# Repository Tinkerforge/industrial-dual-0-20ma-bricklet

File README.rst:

Industrial Dual 0-20mA Bricklet
===============================

This repository contains the firmware source code and the hardware design
files. The documentation generator configs can be found at
https://github.com/Tinkerforge/generators

Repository Content
------------------

software/:
 * examples/: Examples for all supported languages
 * build/: Compiled files
 * src/: Source code of firmware
 * Makefile: Makefile to build project

hardware/:
 * Contains KiCad project files and additionally schematics as PDF

datasheets/:
 * Contains datasheets for sensors and complex ICs that are used

Hardware
--------

The hardware is designed with the open source EDA Suite KiCad
(http://www.kicad.org). Before you are able to open the files,
you have to install the Tinkerforge kicad-libraries
(https://github.com/Tinkerforge/kicad-libraries). You can either clone
them directly in hardware/ or clone them in a separate folder and
symlink them into hardware/
(ln -s kicad_path/kicad-libraries project_path/hardware). After that you
can open the .pro file in hardware/ with KiCad and from there view and
modify the schematics and the PCB layout.

Software
--------

If you want to do your own Brick/Bricklet firmware development we highly
recommend that you use our build environment setup script and read the
tutorial (https://www.tinkerforge.com/en/doc/Tutorials/Tutorial_Build_Environment/Tutorial.html).

To compile the C code we recommend you to install the newest GNU Arm Embedded
Toolchain (https://launchpad.net/gcc-arm-embedded/+download).
You also need to install bricklib (https://github.com/Tinkerforge/bricklib)
and brickletlib (https://github.com/Tinkerforge/brickletlib).

You can either clone it directly in software/src/ or clone it in a
separate folder and symlink it into software/src/
(ln -s bricklib_path/bricklib project_path/software/src/ and
ln -s brickletlib_path/brickletlib project_path/software/src/).
Finally make sure to have CMake installed
(http://www.cmake.org/cmake/resources/software.html).

After that you can build the firmware by invoking make in software/.
The firmware (.bin) can then be found in software/build/ and uploaded
with brickv (click button "Flashing" on start screen).

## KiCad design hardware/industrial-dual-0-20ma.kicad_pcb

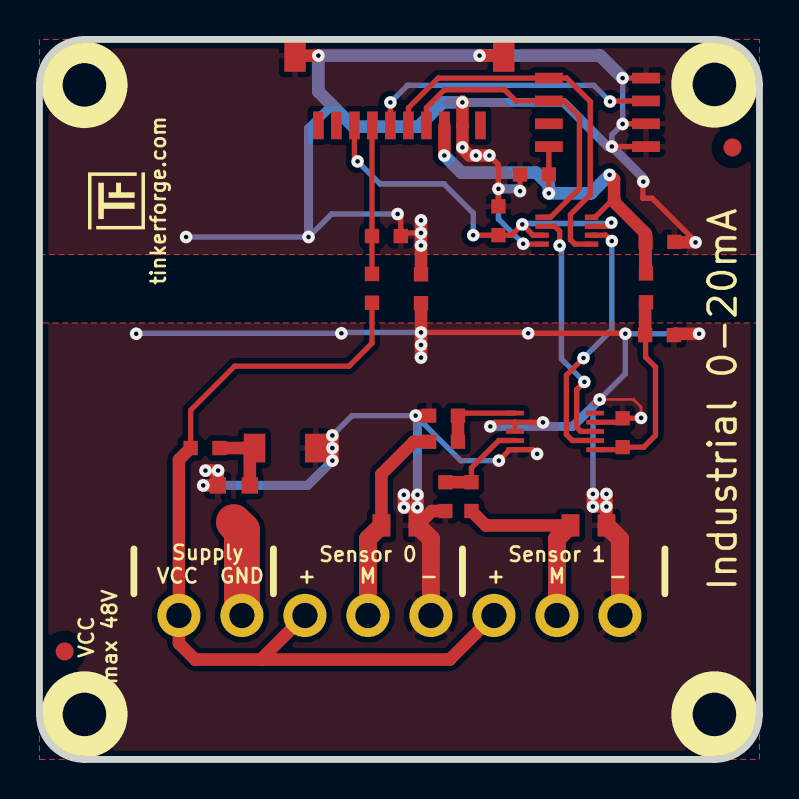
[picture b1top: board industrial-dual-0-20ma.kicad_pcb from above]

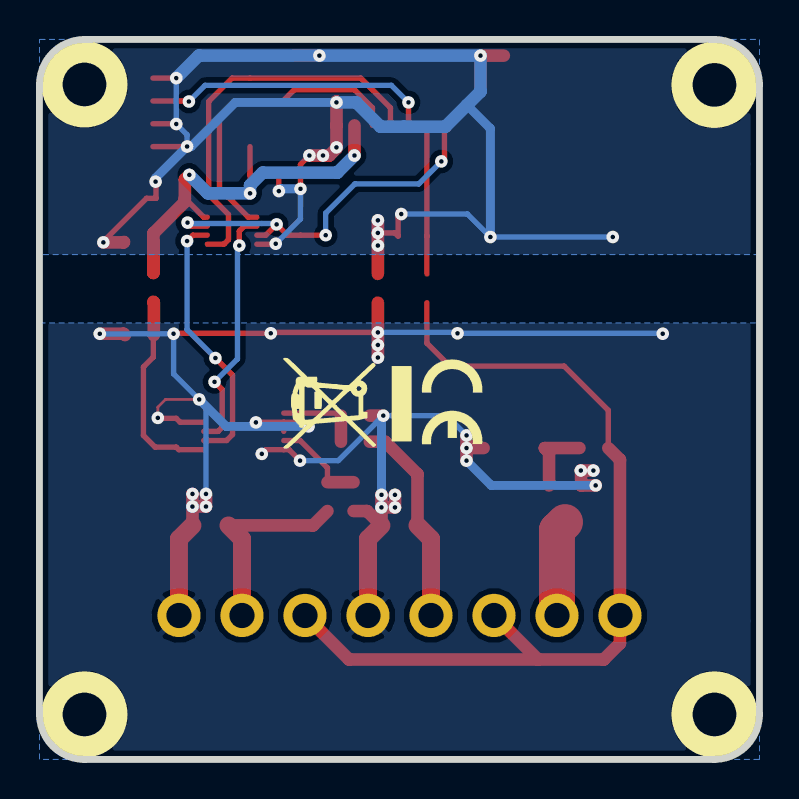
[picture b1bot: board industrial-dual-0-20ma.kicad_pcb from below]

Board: 2 copper layers, 40.0 x 40.0 mm, 31 parts (2 on the bottom side), 18 nets.

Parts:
C1, C3, C4, C5, C6: 100nF; C0603
C2: 1µF; C0603
D1: Z12V; MiniMelf
FB1, FB2: FB; C0603
Fiducial_Mark: VAL**; Fiducial_Mark
Fiducial_Mark#2: VAL**; Fiducial_Mark
P1: CON-SENSOR
P2: P-PWR-8GN; OQ_8P
Q1: FDN5630; SOT23GDS
R1, R4, R5: 1k; R0603
R2: 6k8; R0603
R3: 10k; R0603
R6, R7: 91/25ppm; R0805
R8: 100k; R0603
U1: M24C64; SOIC8
U2: NC7WB66K8X; VSSOP8
U3: MCP3423; MSOP10-0.5
U4, U5, U6, U7: DRILL; DRILL_NP
VAL: CE_5mm
VAL#2: WEEE_7mm

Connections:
3V3: C1.1, C3.1, FB1.2, P1.3, U1.8, U2.8
+3.3VP: C2.2, C4.1, FB1.1, U3.6
AGND: C2.1, C4.2, C5.1, C6.1, D1.1, FB2.1, P2.5, P2.8, Q1.S, R6.2, R7.2, U3.2, U3.3, U3.5, U3.9
GND: C1.2, C3.2, FB2.2, P1.2, P1.EP, R1.1, R3.1, U1.1, U1.2, U1.4, U2.4
MEASURE: P2.1, P2.3, P2.6, R2.1, R8.1
unnamed: C5.2, R4.1, U3.1
unnamed: C6.2, R5.1, U3.4
unnamed: D1.2, Q1.G, R8.2
unnamed: P1.6, U1.3
unnamed: P1.7, R1.2, R2.2
unnamed: P1.8, R3.2, U2.3, U2.7
unnamed: P2.2, Q1.D
unnamed: P2.4, R4.2, R7.1
unnamed: P2.7, R5.2, R6.1
SCL: P1.4, U1.6, U2.1
SCL2: U2.2, U3.8
SDA: P1.5, U1.5, U2.5
SDA2: U2.6, U3.7

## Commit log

2013-06-20 Add examples for Industrial Dual 0-20mA Bricklet
2013-06-25 Hardware Files Checkin
2013-07-04 Fix naming
2013-07-17 Break long lines
2013-08-12 Add shell examples
2013-08-21 windows: Don't trigger a build in generate_makefile.bat
    Also use normal make instead of a special named one.
2013-12-19 Fix wrong length for GetDebounce packet (through brickletlib) Add select for MCP3422
2014-01-06 Add static assert for BrickContext size
2014-01-10 Add Perl examples
2014-01-15 php: Use const for constant values
2014-02-07 Add Mathematica examples
2014-02-10 perl: fixed namespace
2014-02-11 javascript: add examples
2014-02-11 javascript: short examples
2014-02-18 javascript: examples fixed
2014-02-20 javascript: add html examples
2014-02-24 javascript: port 4280, startExample()
2014-02-28 javascript: Break long lines and cleanup whitespace
2014-03-05 Add LabVIEW examples
2014-03-06 labview: Add examples in LV2010 format
2014-03-25 matlab: add examples
2014-04-02 java: Unify constants style
2014-04-02 perl: Unify print style
2014-04-17 matlab: Adapt examples to new callback style
2014-04-17 Fix typos
2014-04-17 matlab: Add parentheses to make pygments happy
2014-04-17 matlab: Fix string in Octave
2014-07-03 Fix typo
2014-07-15 java: Replace System.console() usage with an Eclipse compatible pattern
2014-12-02 Use ReadLine instead of ReadKey for C# example
2015-02-13 vbnet: Use ReadLine instead of ReadKey
    Because ReadKey doesn't work with a pipe as stdin on the RED Brick.
2015-03-02 windows: Stop cmake from searching for mingw32-make.exe
    Using MinGW Makefiles as generator makes cmake search for mingw32-make.exe
    which might not be installed because GnuWin32's make.exe is used instead.
2015-04-09 c: Whitespace
2015-06-18 Break long lines in examples
2015-06-18 Fix typos in Mathematica and LabVIEW examples
2015-06-24 javascript: Clean up output creation
2015-06-29 octave: Handle short difference between Octave 3.6 and 3.8
    In Octave 3.6 a short is not automatically handled as a number.
2015-07-23 Make JavaScript browser example textarea readonly
2015-07-27 Cleanup C/C++, C#, Java and Python examples
2015-07-29 Reformat changelog
2015-07-30 Cleanup C/C++, C#, Java, Python and Ruby examples more
2015-08-07 Use full device class name in Python examples
2015-08-12 Fix minor warnings in C/C++ examples
2015-08-17 Cleanup Delphi examples
2015-08-18 Cleanup VB.NET examples
2015-08-19 Cleanup Perl examples
2015-09-09 Duplicate cmake call to fix bug during cmake creation
2015-10-16 Generator based example cleanup
2015-11-12 matlab: Fix callback handling for R2014a
    http://undocumentedmatlab.com/blog/matlab-callbacks-for-java-events-in-r2014a
2015-11-25 Include date and commit into changelog
2015-11-30 vbnet: Shorten long line
2016-05-18 c: Add missing device destroy call
2016-06-29 Whitespace
2016-07-01 Make the change UID comment more explicit
2017-04-13 csharp: Adapt example
2017-04-21 shell: Adapt example
2017-06-02 octave: Use javaObject instead of deprecated java_new
2017-06-12 set mcp3423 pin ADR1 to floating
2017-06-30 Add 3d information (final)
2017-06-30 Add 3d model (*.step and *.FCStd)
2017-07-07 Rename *.FCStd file
2017-11-30 Update examples from generator
2017-12-07 mathematica: Also generate .nb files
2018-01-26 c: Fine-tune printf format
2018-02-02 Update examples
2018-02-19 javascript: Close div tag correctly
2018-02-20 Add .gitignore
2018-02-20 Cleanup KiCad libraries config
    Ensure LibDir=kicad-libraries and LibName1=tinkerforge.
    Remove special library.
2018-05-11 Rename files
2018-05-24 perl: Use strict in examples
2018-07-11 Add Makefile with docker support
2018-07-11 Remove obsolete generate_makefile scripts
2018-07-11 Update directory structure and build instructions
2018-07-16 Fix name collision with "select" function in newlib
2018-09-14 vbnet: Fix typo in comment
2018-11-06 Add rust examples
2018-11-07 rust: Accept host names for ip connection, fix naming inconsistencies
2018-11-07 rust: Rename callback receivers.
2018-12-14 Add go examples.
2018-12-14 go: Fix printf parameters.
2018-12-18 go: Change import path.
2018-12-18 go: Change import path again.
2018-12-20 rust: Reformat examples.
2019-01-24 mqtt: Add examples.
2019-01-24 mqtt: Fix example header.
2019-01-24 mqtt: Remove executable bit in example permissions.
2019-01-24 go: Minor example fixes.
2019-01-24 mqtt: Minor example fixes.
2019-03-25 mqtt: Fix example whitespace.
2019-03-28 mqtt: Fix whitespace.
2019-08-22 c: Adapt to bindings changes
2020-01-13 examples: Use python3 input instead of python2 raw_input.
2020-01-13 examples: mqtt: Remove trailing whitespace.
2020-04-14 mqtt: Fix device name format
2021-10-25 Update KiCad link
    https://www.kicad.org/blog/2021/10/Avoid-links-to-former-kicad-domain/
2022-07-06 Add license files.

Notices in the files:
hardware/industrial-dual-0-20ma.kicad_pcb:
Licensed under CERN OHL v.1.1
Copyright (©) 2013, B.Nordmeyer
Copyright Tinkerforge GmbH 2013.
This documentation describes Open Hardware and is licensed under the
CERN OHL v. 1.1.
